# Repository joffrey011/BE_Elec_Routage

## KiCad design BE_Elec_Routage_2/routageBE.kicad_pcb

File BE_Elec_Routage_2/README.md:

# BE_Elec_Routage
Doly Joffrey, Urben Baptiste

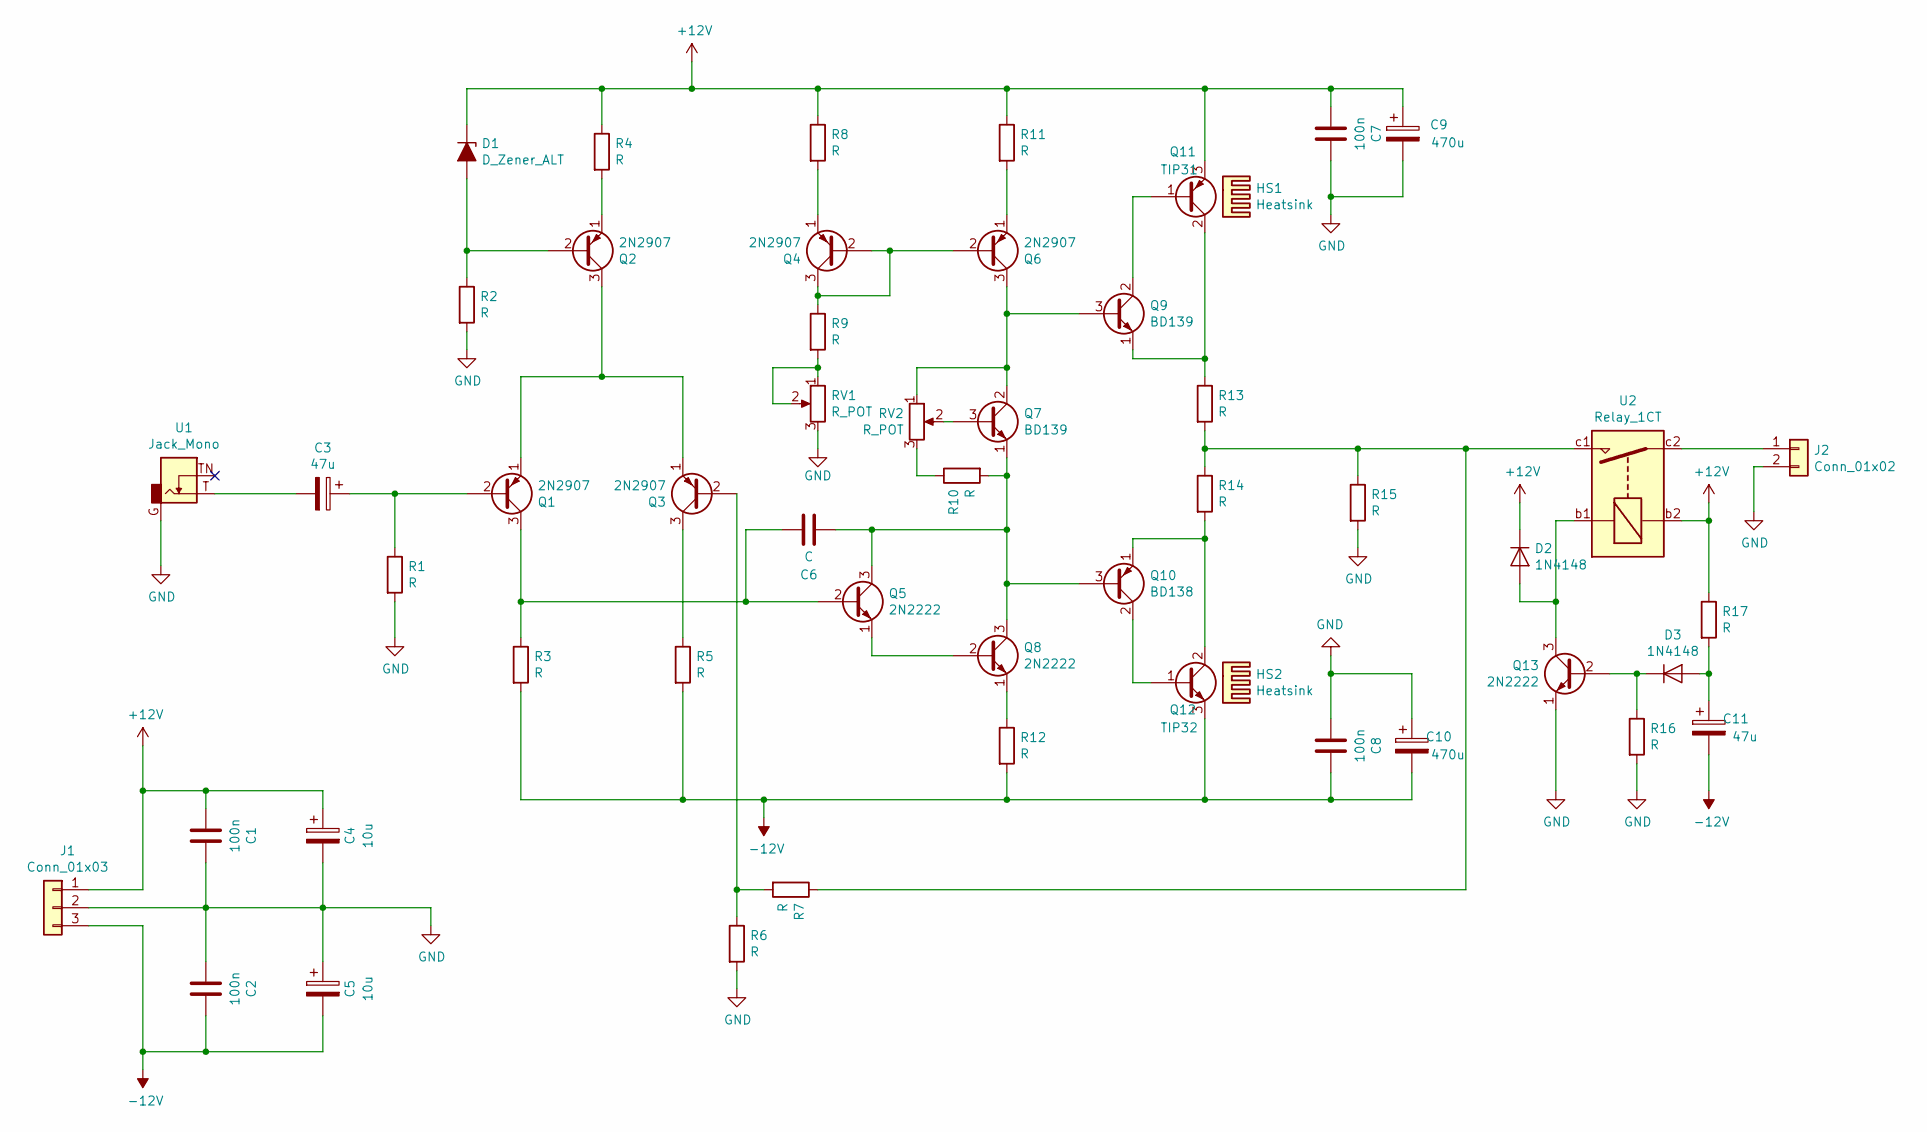
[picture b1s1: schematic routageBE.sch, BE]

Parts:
C1, C2, C7, C8: 100n; C_Rect_L7.2mm_W3.5mm_P5.00mm_FKS2_FKP2_MKS2_MKP2
C3, C11: 47u; CP_Radial_D8.0mm_P5.00mm
C4, C5: 10u; CP_Radial_D8.0mm_P5.00mm
C6: C; C_Rect_L7.2mm_W3.5mm_P5.00mm_FKS2_FKP2_MKS2_MKP2
C9, C10: 470u; CP_Radial_D12.5mm_P5.00mm
D1: D_Zener_ALT; D_DO-35_SOD27_P10.16mm_Horizontal
D2, D3: 1N4148; D_DO-35_SOD27_P10.16mm_Horizontal
HS1, HS2: Heatsink; Heatsink_Fischer_SK104-STC-STIC_35x13mm_2xDrill2.5mm
J1: Conn_01x03; PhoenixContact_MSTBVA_2,5_3-G-5,08_1x03_P5.08mm_Vertical
J2: Conn_01x02; PhoenixContact_MSTBVA_2,5_2-G-5,08_1x02_P5.08mm_Vertical
Q1, Q2, Q3, Q4, Q6: 2N2907; TO-18-3
Q5, Q8, Q13: 2N2222; TO-18-3
Q7, Q9: BD139; TO-126-3_Vertical
Q10: BD138; TO-126-3_Vertical
Q11: TIP31; TO-220-3_Vertical
Q12: TIP32; TO-220-3_Vertical
R1, R2, R3, R4, R5, R6, R7, R8, R9, R10, R11, R12, R15, R16, R17: R; R_Axial_DIN0207_L6.3mm_D2.5mm_P10.16mm_Horizontal
R13, R14: R; R_Axial_DIN0516_L15.5mm_D5.0mm_P20.32mm_Horizontal
RV1, RV2: R_POT; Potentiometer_Bourns_3296W_Vertical
U1: Jack_Mono; Jack_35RAPC2AV
U2: Relay_1CT; Relai_BE

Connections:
+12V: C1.2, C4.1, C7.2, C9.1, D1.1 (K), D2.1 (K), J1.1, Q11.3 (E), R4.1, R8.1, R11.1, R17.1, U2.b2
-12V: C2.1, C5.2, C8.1, C10.2, C11.2, J1.3, Q12.3 (E), R3.2, R5.2, R12.2
GND: C1.1, C2.2, C4.2, C5.1, C7.1, C8.2, C9.2, C10.1, J1.2, J2.2, Q13.1 (E), R1.2, R2.2, R6.2, R15.2, R16.2, RV1.3, U1.G
unnamed: C3.1, Q1.2 (B), R1.1
unnamed: C3.2, U1.T
unnamed: C6.1, Q5.3 (C), Q7.1 (E), Q8.3 (C), Q10.3 (B), R10.2
unnamed: C6.2, Q1.3 (C), Q5.2 (B), R3.1
unnamed: C11.1, D3.2 (A), R17.2
unnamed: D1.2 (A), Q2.2 (B), R2.1
unnamed: D2.2 (A), Q13.3 (C), U2.b1
unnamed: D3.1 (K), Q13.2 (B), R16.1
unnamed: J2.1, U2.c2
unnamed: Q1.1 (E), Q2.3 (C), Q3.1 (E)
unnamed: Q2.1 (E), R4.2
unnamed: Q3.2 (B), R6.1, R7.2
unnamed: Q3.3 (C), R5.1
unnamed: Q4.1 (E), R8.2
unnamed: Q4.2 (B), Q4.3 (C), Q6.2 (B), R9.1
unnamed: Q5.1 (E), Q8.2 (B)
unnamed: Q6.1 (E), R11.2
unnamed: Q6.3 (C), Q7.2 (C), Q9.3 (B), RV2.1
unnamed: Q7.3 (B), RV2.2
unnamed: Q8.1 (E), R12.1
unnamed: Q10.1 (E), Q12.2 (C), R14.2
unnamed: Q10.2 (C), Q12.1 (B)
unnamed: Q9.2 (C), Q11.1 (B)
unnamed: Q9.1 (E), Q11.2 (C), R13.1
unnamed: R9.2, RV1.1, RV1.2
unnamed: R10.1, RV2.3
unnamed: R7.1, R13.2, R14.1, R15.1, U2.c1

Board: 2 copper layers, 52 parts (0 on the bottom side), 30 nets, no tracks yet.

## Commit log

2020-03-23 schema sauf relay
2020-04-02 empreinte relai
2020-04-17 placement
